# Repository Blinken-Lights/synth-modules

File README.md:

# synth-modules
Synth module schematics and code

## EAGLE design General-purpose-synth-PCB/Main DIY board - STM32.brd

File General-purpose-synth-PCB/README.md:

A perfboard/breadboard style PCB, to be used as a basis for any DIY module. Including a few common circuit features to speed up DIY'ing.
It's designed to connect to the rear of a module panel at 90 degrees, via the potentiometer and jack socket nuts.

- 16mm potentiometer footprints (cheapest type of potentiometer)
-- 90 degree potentiometer brackets to take the strain off the solder joints
- 3.5mm stereo jack socket footprints
- 10 pin Eurorack power connector
- 7085 voltage regulator
- voltage reference IC
- Arduino Nano footprint

The Arduino, voltage reference and power ICs are all connected via the PCB.
The PCB should also be useful for 100% analogue modules too.

**UPDATE 18th May**

- Uploaded Arduino board without 3V3 supply, with option to break out SCK and MOSI to the central rails
- Uploaded STM32 blue pill based board
- Created MIDI daughter board, fitting behind 2 jacks that can be screwed into a front panel
- Uploaded .zip files containing gerber and excellon files, that are ready for CAM
- All this is still **UNTESTED!**

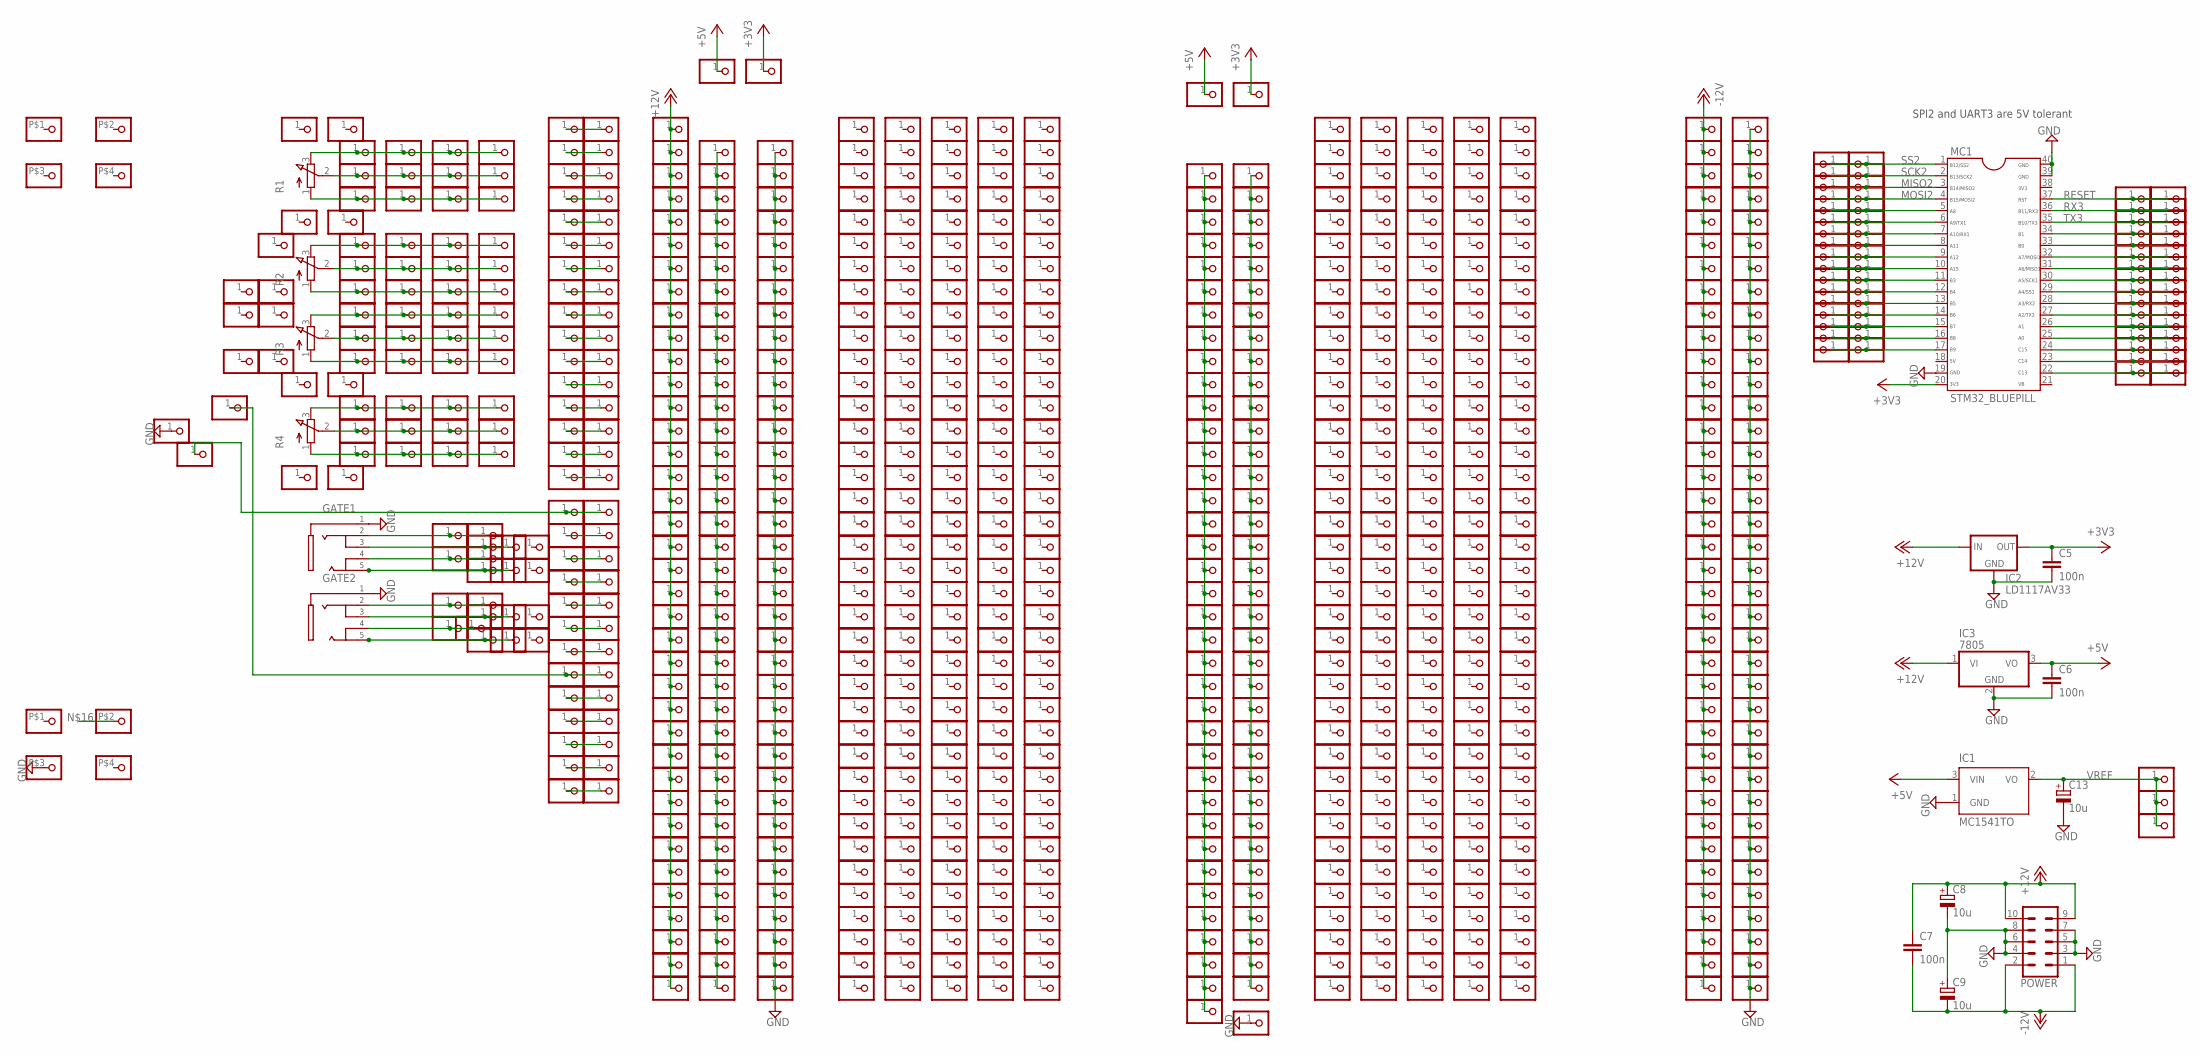
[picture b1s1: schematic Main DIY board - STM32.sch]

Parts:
C5, C6, C7: 100n; C050-025X075
C8, C9, C13: 10u; E2,5-5
GATE1, GATE2: PJ-324MH
IC1: MC1541TO; TO92
IC2: LD1117AV33; 78XXL
IC3: 7805; TO220H
JP1, JP2, JP3, JP4, JP5, JP6, JP7, JP8, JP9, JP10, JP11, JP12, JP13, JP14, JP15, JP16, JP17, JP18, JP19, JP20, JP21, JP22, JP23, JP24, JP25, JP26, JP27, JP28, JP29, JP30, JP31, JP32, JP33, JP34, JP35, JP36, JP37, JP38, JP39, JP40, JP41, JP42, JP43, JP44, JP45, JP46, JP47, JP48, JP49, JP50, JP51, JP52, JP53, JP54, JP55, JP56, JP57, JP58, JP59, JP60, JP61, JP62, JP63, JP64, JP65, JP66, JP67, JP68, JP69, JP70, JP71, JP72, JP73, JP74, JP75, JP76, JP77, JP78, JP79, JP80, JP81, JP82, JP83, JP84, JP85, JP86, JP87, JP88, JP89, JP90, JP91, JP92, JP93, JP94, JP95, JP96, JP97, JP98, JP99, JP100, JP101, JP102, JP103, JP104, JP105, JP106, JP107, JP108, JP109, JP110, JP111, JP112, JP113, JP114, JP115, JP116, JP117, JP118, JP119, JP120, JP121, JP122, JP123, JP124, JP125, JP126, JP127, JP128, JP129, JP130, JP131, JP132, JP133, JP134, JP135, JP136, JP137, JP138, JP139, JP140, JP141, JP142, JP143, JP144, JP145, JP146, JP147, JP148, JP149, JP150, JP151, JP152, JP153, JP154, JP155, JP156, JP157, JP158, JP159, JP160, JP161, JP162, JP163, JP164, JP165, JP166, JP167, JP168, JP169, JP170, JP171, JP172, JP173, JP174, JP175, JP176, JP177, JP178, JP179, JP180, JP181, JP182, JP183, JP184, JP185, JP186, JP187, JP188, JP189, JP190, JP191, JP192, JP193, JP194, JP195, JP196, JP197, JP198, JP199, JP200, JP201, JP202, JP203, JP204, JP205, JP206, JP207, JP208, JP209, JP210, JP211, JP212, JP213, JP214, JP215, JP216, JP217, JP218, JP219, JP220, JP221, JP222, JP223, JP224, JP225, JP226, JP227, JP228, JP229, JP230, JP231, JP232, JP233, JP234, JP235, JP236, JP237, JP238, JP239, JP240, JP241, JP242, JP243, JP244, JP245, JP246, JP247, JP248, JP249, JP250, JP251, JP252, JP253, JP254, JP255, JP256, JP257, JP258, JP259, JP260, JP261, JP262, JP263, JP264, JP265, JP266, JP267, JP268, JP269, JP270, JP271, JP272, JP273, JP274, JP275, JP276, JP277, JP278, JP279, JP280, JP281, JP282, JP283, JP284, JP285, JP286, JP287, JP288, JP289, JP290, JP291, JP292, JP293, JP294, JP295, JP296, JP297, JP298, JP299, JP300, JP301, JP302, JP303, JP304, JP305, JP306, JP307, JP308, JP309, JP310, JP311, JP312, JP313, JP314, JP315, JP316, JP317, JP318, JP319, JP320, JP321, JP322, JP323, JP324, JP325, JP326, JP327, JP328, JP329, JP330, JP331, JP332, JP333, JP334, JP335, JP336, JP337, JP338, JP339, JP340, JP341, JP342, JP343, JP344, JP345, JP346, JP347, JP348, JP349, JP350, JP351, JP352, JP353, JP354, JP355, JP356, JP357, JP358, JP359, JP360, JP361, JP362, JP363, JP364, JP365, JP366, JP367, JP368, JP369, JP370, JP371, JP372, JP373, JP374, JP375, JP376, JP377, JP378, JP379, JP380, JP381, JP382, JP383, JP384, JP385, JP386, JP387, JP388, JP389, JP390, JP391, JP392, JP393, JP394, JP395, JP396, JP397, JP398, JP399, JP400, JP401, JP402, JP403, JP404, JP405, JP406, JP407, JP408, JP409, JP410, JP411, JP412, JP413, JP414, JP415, JP416, JP417, JP418, JP419, JP420, JP421, JP422, JP423, JP424, JP425, JP426, JP427, JP428, JP429, JP430, JP431, JP432, JP433, JP434, JP435, JP436, JP437, JP438, JP439, JP440, JP441, JP442, JP443, JP444, JP445, JP446, JP447, JP448, JP449, JP450, JP451, JP452, JP453, JP454, JP455, JP456, JP457, JP458, JP459, JP460, JP461, JP462, JP463, JP464, JP465, JP466, JP467, JP468, JP469, JP470, JP471, JP472, JP473, JP474, JP475, JP476, JP477, JP478, JP479, JP480, JP481, JP482, JP483, JP484, JP485, JP486, JP487, JP488, JP489, JP490, JP491, JP492, JP493, JP494, JP495, JP496, JP497, JP498, JP499, JP500, JP501, JP502, JP503, JP504, JP505, JP506, JP507, JP508, JP509, JP510, JP511, JP512, JP513, JP514, JP515, JP516, JP517, JP518, JP519, JP520, JP521, JP522, JP523, JP524, JP525, JP526, JP527, JP528, JP529, JP530, JP531, JP532, JP533, JP534, JP535, JP536, JP537, JP538, JP539, JP540, JP541, JP542, JP543, JP544, JP545, JP546, JP547, JP548, JP549, JP550, JP551, JP552, JP553, JP554, JP555, JP556, JP557, JP558, JP559, JP560, JP561, JP562, JP563, JP564, JP565, JP566, JP567, JP568, JP569, JP570, JP571, JP572, JP573, JP574, JP575, JP576, JP577, JP578, JP579, JP580, JP581, JP582, JP583, JP584, JP585, JP586, JP587, JP588, JP589, JP590, JP591, JP592, JP593, JP594, JP595, JP596, JP597, JP598, JP599, JP600, JP601, JP602, JP603, JP604, JP605, JP606, JP607, JP608, JP609, JP610, JP611, JP612, JP613, JP614, JP615, JP616, JP617, JP618, JP619, JP620, JP621, JP622, JP623, JP624, JP625, JP626, JP627, JP628, JP629, JP630, JP631, JP632, JP633, JP634, JP635, JP636, JP637, JP638, JP639, JP640, JP641, JP642, JP643, JP644, JP645, JP646, JP647, JP648, JP649, JP650, JP651, JP652, JP653, JP654, JP655, JP656, JP657, JP658, JP659, JP660, JP661, JP662, JP663, JP664, JP665, JP666, JP667, JP668, JP669, JP670, JP671, JP672, JP673, JP674, JP675, JP676, JP677, JP678, JP679, JP680, JP681, JP682, JP683, JP684, JP685, JP686, JP687, JP688, JP689, JP690, JP691, JP692, JP693, JP694, JP695, JP696, JP697, JP698, JP699, JP700, JP701, JP702, JP703, JP704, JP705, JP706, JP707, JP708, JP709, JP710, JP711, JP712, JP713, JP714, JP715, JP716, JP717, JP718, JP719, JP720, JP721, JP722, JP723, JP724, JP725, JP726, JP727, JP728, JP729, JP730, JP731, JP732, JP733, JP734, JP735, JP736, JP737, JP738, JP739, JP740, JP741, JP742, JP743, JP744, JP745, JP746, JP747, JP748, JP749, JP750, JP751, JP752, JP753, JP754, JP755, JP756, JP757, JP758, JP759, JP760, JP761, JP762, JP763, JP764, JP765, JP766, JP767, JP768, JP769, JP770, JP771, JP772, JP773, JP774, JP775, JP776, JP777, JP778, JP779, JP780, JP781, JP782, JP783, JP784, JP785, JP786, JP787, JP791, JP792, JP793, JP794, JP795, JP796, JP797, JP798, JP799, JP800, JP801, JP802, JP803, JP804, JP805, JP806, JP807, JP808, JP809, JP810, JP811, JP812, JP813, JP814, JP815, JP816, JP817, JP818, JP819, JP820, JP821, JP822, JP823, JP824, JP825, JP826, JP827, JP828, JP829, JP830, JP831, JP832, JP833, JP834, JP835, JP836, JP837, JP838, JP839, JP840, JP841, JP842, JP843, JP844, JP845, JP846, JP847, JP848, JP849, JP850, JP851, JP852, JP853, JP854, JP855, JP856, JP857, JP858, JP859: 1X01
JP788, JP789, JP790: 1X01-WIDE
MC1: STM32_BLUEPILL
POWER: CONN_05X2SHD; 2X5-SHROUDED
R1, R2, R3, R4: 3RP/1610N
U$1, U$2: RIGHTANGLE

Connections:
+3V3: C5.1, IC2.GND (OUT), JP345.1, JP779.1, MC1.20
+5V: C6.1, IC1.3 (VIN), IC3.3 (VO), JP344.1, JP778.1
+12V: C7.1, C8.+, IC2.OUT (IN), IC3.1 (VI), JP114.1, JP115.1, JP117.1, JP118.1, JP119.1, JP120.1, JP121.1, JP122.1, JP123.1, JP124.1, JP125.1, JP126.1, JP127.1, JP128.1, JP129.1, JP130.1, JP131.1, JP132.1, JP133.1, JP134.1, JP135.1, JP136.1, JP137.1, JP138.1, JP139.1, JP140.1, JP141.1, JP142.1, JP143.1, JP144.1, JP145.1, JP146.1, JP147.1, JP148.1, JP149.1, JP150.1, JP151.1, JP152.1, POWER.9, POWER.10
-12V: C7.2, C9.-, JP267.1, JP268.1, JP269.1, JP270.1, JP271.1, JP272.1, JP273.1, JP274.1, JP275.1, JP276.1, JP277.1, JP278.1, JP279.1, JP280.1, JP281.1, JP282.1, JP283.1, JP284.1, JP285.1, JP286.1, JP287.1, JP288.1, JP289.1, JP290.1, JP291.1, JP292.1, JP293.1, JP294.1, JP295.1, JP296.1, JP297.1, JP298.1, JP299.1, JP300.1, JP301.1, JP302.1, JP303.1, JP304.1, POWER.1, POWER.2
GND: C5.2, C6.2, C8.-, C9.+, C13.-, GATE1.1, GATE2.1, IC1.1 (GND), IC2.IN (GND), IC3.2 (GND), JP154.1, JP155.1, JP156.1, JP157.1, JP158.1, JP159.1, JP160.1, JP161.1, JP162.1, JP163.1, JP164.1, JP165.1, JP166.1, JP167.1, JP168.1, JP169.1, JP170.1, JP171.1, JP172.1, JP173.1, JP174.1, JP175.1, JP176.1, JP177.1, JP178.1, JP179.1, JP180.1, JP181.1, JP182.1, JP183.1, JP184.1, JP185.1, JP186.1, JP187.1, JP188.1, JP189.1, JP190.1, JP305.1, JP306.1, JP307.1, JP308.1, JP309.1, JP310.1, JP311.1, JP312.1, JP313.1, JP314.1, JP315.1, JP316.1, JP317.1, JP318.1, JP319.1, JP320.1, JP321.1, JP322.1, JP323.1, JP324.1, JP325.1, JP326.1, JP327.1, JP328.1, JP329.1, JP330.1, JP331.1, JP332.1, JP333.1, JP334.1, JP335.1, JP336.1, JP337.1, JP338.1, JP339.1, JP340.1, JP341.1, JP342.1, JP343.1, JP788.1, MC1.19, MC1.39, MC1.40, POWER.3, POWER.4, POWER.5, POWER.6, POWER.7, POWER.8, U$2.P$3
MISO2: JP798.1, JP799.1, MC1.3
MOSI2: JP800.1, JP801.1, MC1.4
unnamed: JP14.1, JP15.1, JP16.1, JP51.1, R2.3 (E)
unnamed: JP2.1, JP3.1, JP5.1, JP45.1, R1.3 (E)
unnamed: JP17.1, JP18.1, JP19.1, JP53.1, R2.2 (S)
unnamed: JP6.1, JP7.1, JP8.1, JP47.1, R1.2 (S)
unnamed: JP9.1, JP10.1, JP11.1, JP49.1, R1.1 (A)
unnamed: JP20.1, JP21.1, JP22.1, JP55.1, R2.1 (A)
unnamed: JP23.1, JP24.1, JP25.1, JP57.1, R3.3 (E)
unnamed: JP26.1, JP27.1, JP28.1, JP59.1, R3.2 (S)
unnamed: JP29.1, JP30.1, JP31.1, JP61.1, R3.1 (A)
unnamed: JP34.1, JP35.1, JP36.1, JP63.1, R4.3 (E)
unnamed: JP37.1, JP38.1, JP39.1, JP65.1, R4.2 (S)
unnamed: JP40.1, JP41.1, JP42.1, JP67.1, R4.1 (A)
unnamed: GATE1.5, JP728.1, JP735.1
unnamed: GATE2.5, JP732.1, JP740.1
unnamed: JP193.1, JP194.1, JP195.1, JP196.1, JP197.1, JP198.1, JP199.1, JP200.1, JP201.1, JP202.1, JP203.1, JP204.1, JP205.1, JP206.1, JP207.1, JP208.1, JP209.1, JP210.1, JP211.1, JP212.1, JP213.1, JP214.1, JP215.1, JP216.1, JP217.1, JP218.1, JP219.1, JP220.1, JP221.1, JP222.1, JP223.1, JP224.1, JP225.1, JP226.1, JP227.1, JP228.1, JP724.1
unnamed: GATE1.2, JP725.1, JP733.1, U$2.P$2
unnamed: JP230.1, JP232.1, JP233.1, JP234.1, JP235.1, JP236.1, JP237.1, JP238.1, JP239.1, JP240.1, JP241.1, JP242.1, JP243.1, JP244.1, JP245.1, JP246.1, JP247.1, JP248.1, JP249.1, JP250.1, JP251.1, JP252.1, JP253.1, JP254.1, JP255.1, JP256.1, JP257.1, JP258.1, JP259.1, JP260.1, JP261.1, JP262.1, JP263.1, JP264.1, JP265.1, JP723.1
unnamed: GATE1.3, JP726.1, JP734.1
unnamed: GATE1.4, JP727.1, JP736.1
unnamed: GATE2.2, JP729.1, JP737.1
unnamed: GATE2.3, JP730.1, JP738.1
unnamed: GATE2.4, JP731.1, JP739.1
unnamed: JP91.1, JP92.1
unnamed: JP742.1, JP743.1, JP744.1, JP745.1, JP746.1, JP747.1, JP748.1, JP749.1, JP750.1, JP751.1, JP752.1, JP753.1, JP754.1, JP755.1, JP756.1, JP757.1, JP758.1, JP759.1, JP760.1, JP761.1, JP762.1, JP763.1, JP764.1, JP765.1, JP766.1, JP767.1, JP768.1, JP769.1, JP770.1, JP771.1, JP772.1, JP773.1, JP774.1, JP775.1, JP776.1, JP777.1, JP780.1
unnamed: JP46.1, JP48.1
unnamed: JP50.1, JP52.1
unnamed: JP54.1, JP56.1
unnamed: JP58.1, JP60.1
unnamed: JP62.1, JP64.1
unnamed: JP66.1, JP68.1
unnamed: JP69.1, JP70.1
unnamed: JP71.1, JP72.1
unnamed: JP73.1, JP74.1
unnamed: JP75.1, JP76.1
unnamed: JP77.1, JP78.1
unnamed: JP79.1, JP80.1
unnamed: JP81.1, JP82.1
unnamed: JP83.1, JP84.1
unnamed: JP85.1, JP86.1
unnamed: JP87.1, JP116.1, JP789.1
unnamed: JP88.1, JP89.1
unnamed: JP90.1, JP93.1
unnamed: JP94.1, JP95.1
unnamed: JP96.1, JP97.1
unnamed: JP98.1, JP99.1
unnamed: JP100.1, JP101.1
unnamed: JP104.1, JP105.1
unnamed: JP106.1, JP107.1
unnamed: JP108.1, JP109.1
unnamed: JP110.1, JP111.1
unnamed: JP112.1, JP113.1
unnamed: JP102.1, JP103.1, JP790.1
unnamed: JP802.1, JP803.1, MC1.5
unnamed: JP804.1, JP805.1, MC1.6
unnamed: JP806.1, JP807.1, MC1.7
unnamed: JP808.1, JP809.1, MC1.8
unnamed: JP810.1, JP811.1, MC1.9
unnamed: JP812.1, JP813.1, MC1.10
unnamed: JP814.1, JP815.1, MC1.11
unnamed: JP816.1, JP817.1, MC1.12
unnamed: JP818.1, JP819.1, MC1.13
unnamed: JP820.1, JP821.1, MC1.14
unnamed: JP822.1, JP823.1, MC1.15
unnamed: JP824.1, JP825.1, MC1.16
unnamed: JP826.1, JP827.1, MC1.17
unnamed: JP834.1, JP835.1, MC1.34
unnamed: JP836.1, JP837.1, MC1.33
unnamed: JP838.1, JP839.1, MC1.32
unnamed: JP840.1, JP841.1, MC1.31
unnamed: JP842.1, JP843.1, MC1.30
unnamed: JP844.1, JP845.1, MC1.29
unnamed: JP846.1, JP847.1, MC1.28
unnamed: JP848.1, JP849.1, MC1.27
unnamed: JP850.1, JP851.1, MC1.26
unnamed: JP852.1, JP853.1, MC1.25
unnamed: JP854.1, JP855.1, MC1.24
unnamed: JP856.1, JP857.1, MC1.23
unnamed: JP858.1, JP859.1, MC1.22
RESET: JP828.1, JP829.1, MC1.37
RX3: JP830.1, JP831.1, MC1.36
SCK2: JP796.1, JP797.1, MC1.2
SS2: JP784.1, JP795.1, MC1.1
TX3: JP832.1, JP833.1, MC1.35
VREF: C13.+, IC1.2 (VO), JP781.1, JP782.1, JP783.1

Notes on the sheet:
SPI2 and UART3 are 5V tolerant

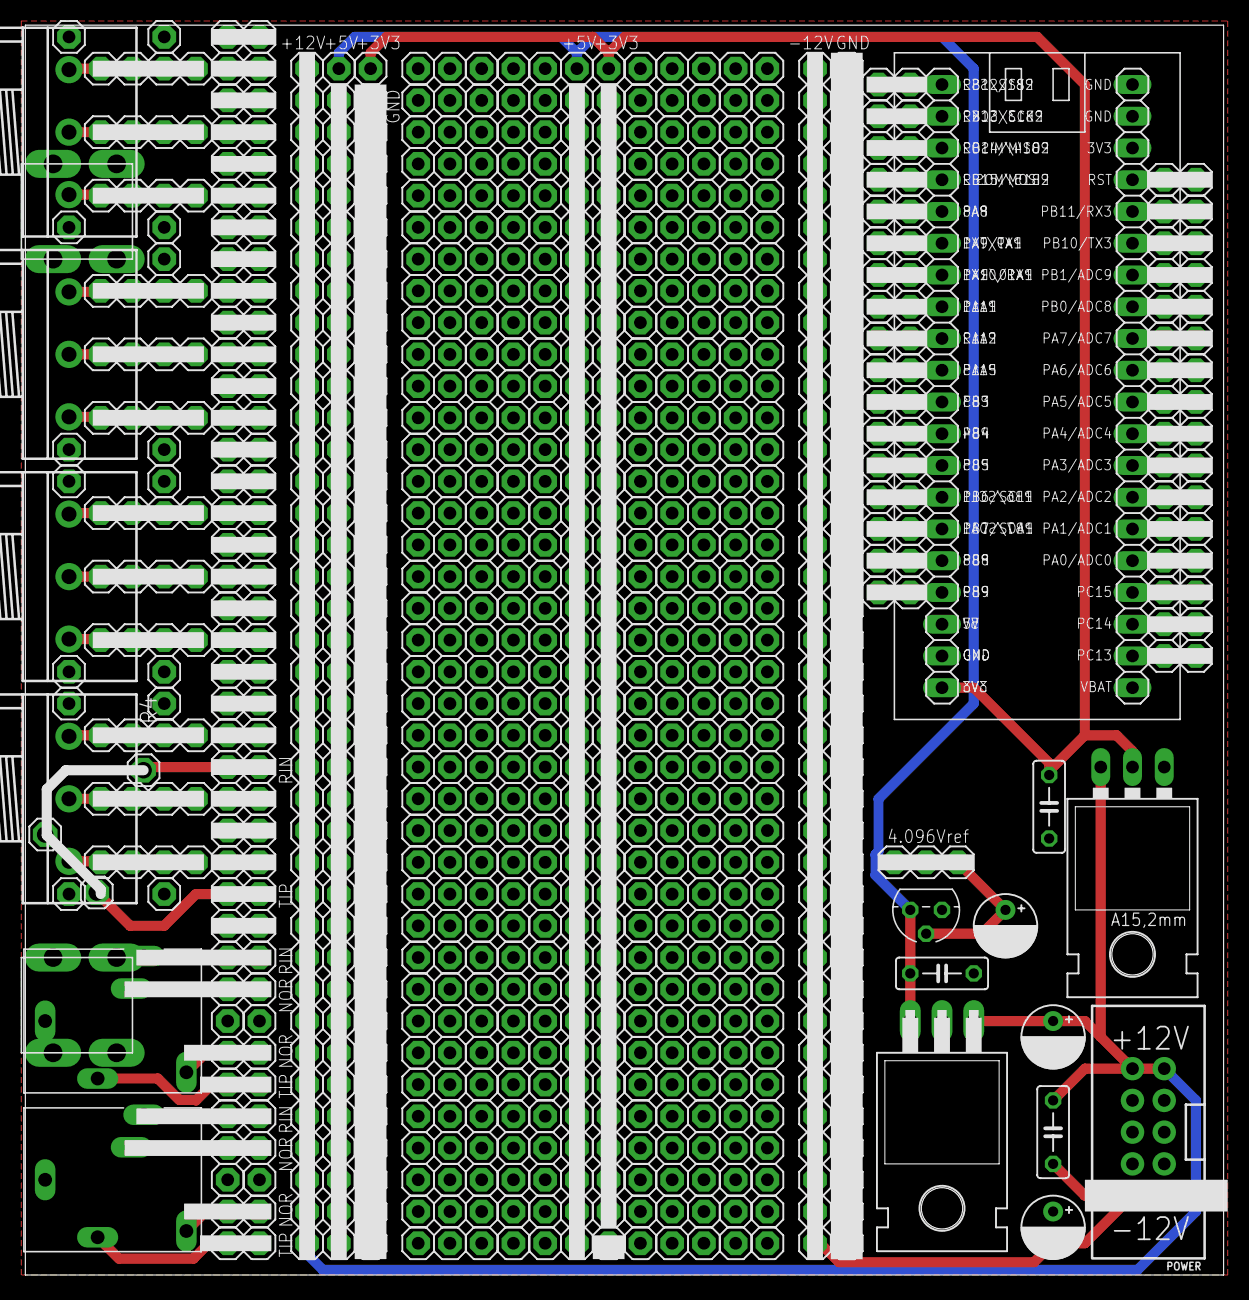
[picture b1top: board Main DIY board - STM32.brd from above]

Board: 2 copper layers, 95.9 x 100.0 mm, 878 parts (0 on the bottom side), 91 nets.

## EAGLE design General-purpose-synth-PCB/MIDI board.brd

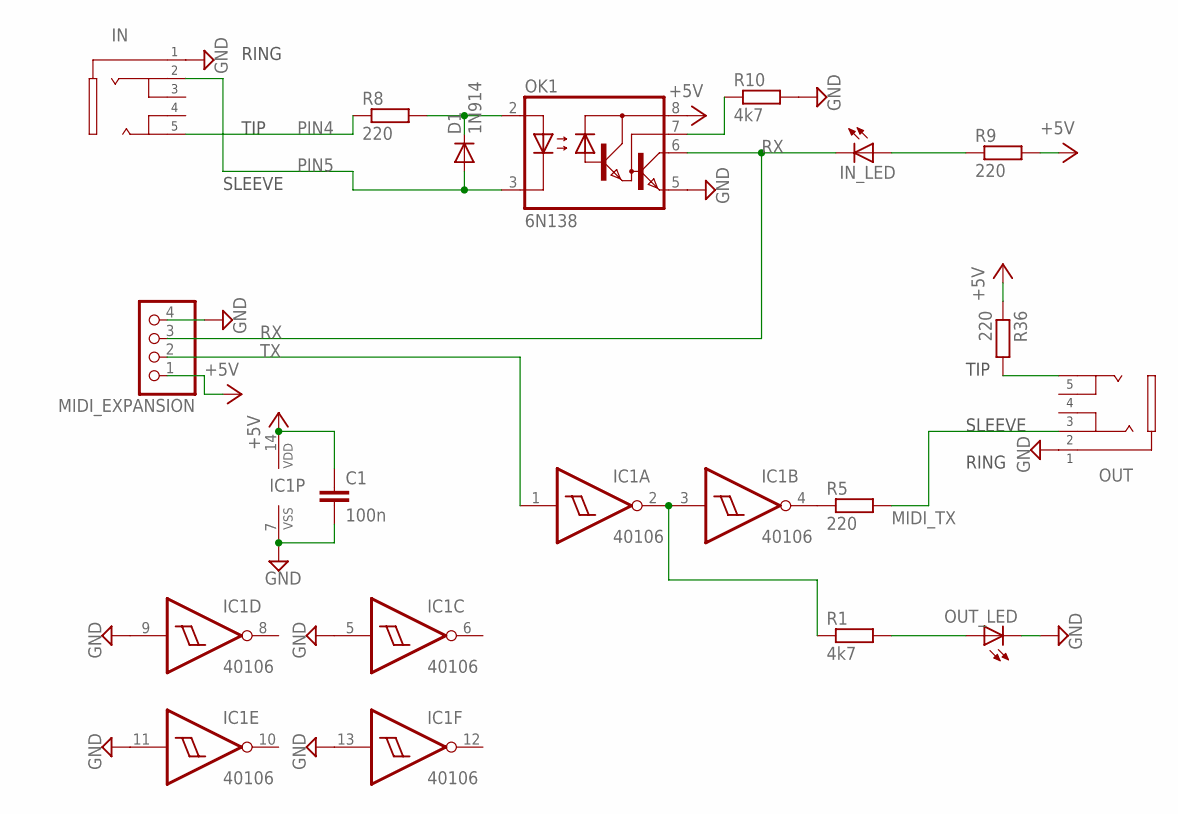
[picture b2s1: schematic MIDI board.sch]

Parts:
C1: 100n; C050-025X075
D1: 1N914; D-6.35
IC1: 40106; DIL14
IN: PJ-324MH
IN_LED: LED3MM-NB; LED3MM
MIDI_EXPANSION: PINHD-1X4; 1X04
OK1: 6N138; DIL08
OUT: PJ-324MH
OUT_LED: LED3MM-NB; LED3MM
R1, R10: 4k7; 0204/7
R5, R8, R9, R36: 220; 0204/7

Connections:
+5V: C1.1, IC1.14 (VDD), MIDI_EXPANSION.1, OK1.8 (VCC), R9.2, R36.1
GND: C1.2, IC1.5 (I), IC1.7 (VSS), IC1.9 (I), IC1.11 (I), IC1.13 (I), IN.1, MIDI_EXPANSION.4, OK1.5 (GND), OUT.1, OUT_LED.K (C), R10.2
MIDI_TX: OUT.2, R5.2
unnamed: OUT_LED.A, R1.2
unnamed: IN_LED.A, R9.1
unnamed: IC1.2 (O), IC1.3 (I), R1.1
unnamed: IC1.4 (O), R5.1
unnamed: OUT.5, R36.2
unnamed: OK1.7 (VB), R10.1
unnamed: D1.C, OK1.2 (A), R8.2
PIN4: IN.5, R8.1
PIN5: D1.A, IN.2, OK1.3 (C)
RX: IN_LED.K (C), MIDI_EXPANSION.3, OK1.6 (VO)
TX: IC1.1 (I), MIDI_EXPANSION.2

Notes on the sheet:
TIP
RING
SLEEVE

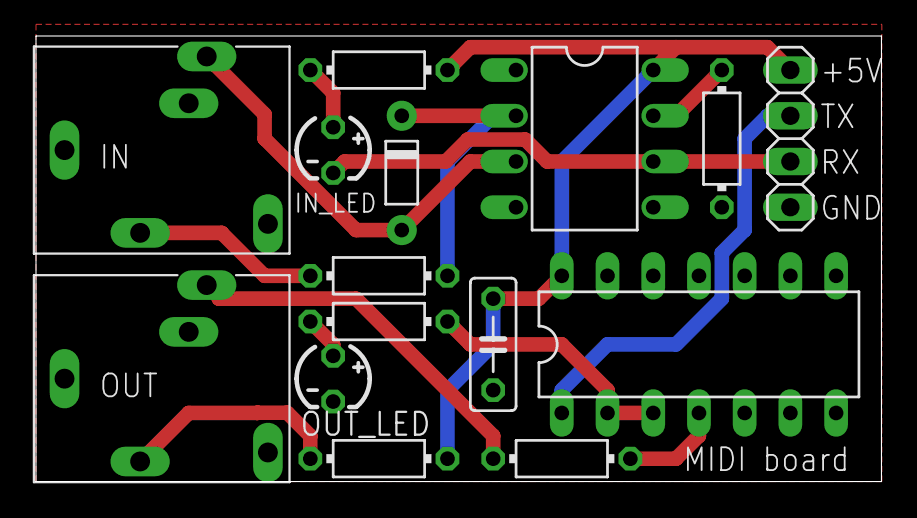
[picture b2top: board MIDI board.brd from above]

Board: 2 copper layers, 47.0 x 24.8 mm, 15 parts (0 on the bottom side), 14 nets.

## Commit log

2020-05-17 Create Meter.ino
    dependency: https://github.com/olikraus/u8glib
2020-05-17 Add files via upload
    Eagle schematic for Meter MIDI sequencer
2020-05-17 Rename STM32 MIDI Expansion.sch to MIDI-daughter-board.sch
2020-05-17 Rename LFO used in rack.sch to LFO-Complex.sch
2022-02-11 Add files via upload
    Add reverse protection diodes to input indicator LEDs
2024-02-08 Add files via upload
    Add capacity for 8 inputs
2024-02-21 Change amplification resistor to 1k8 to avoid clipping
2025-01-17 Create PicoCVAndGates
2025-01-17 Rename PicoCVAndGates to PicoCVAndGates.ino
2025-03-06 Add files via upload
    Upgraded wavetables to 1024 entries long. This reduces the amplitude differences between steps in waves which makes them sound smoother. Also improved the sync feature to make waves slower than one s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

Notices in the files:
parts and their libraries:
SparkFun-IC-Power: Licensing: Creative Commons ShareAlike 4.0 International - https://creativecommons.org/licenses/by-sa/4.0
